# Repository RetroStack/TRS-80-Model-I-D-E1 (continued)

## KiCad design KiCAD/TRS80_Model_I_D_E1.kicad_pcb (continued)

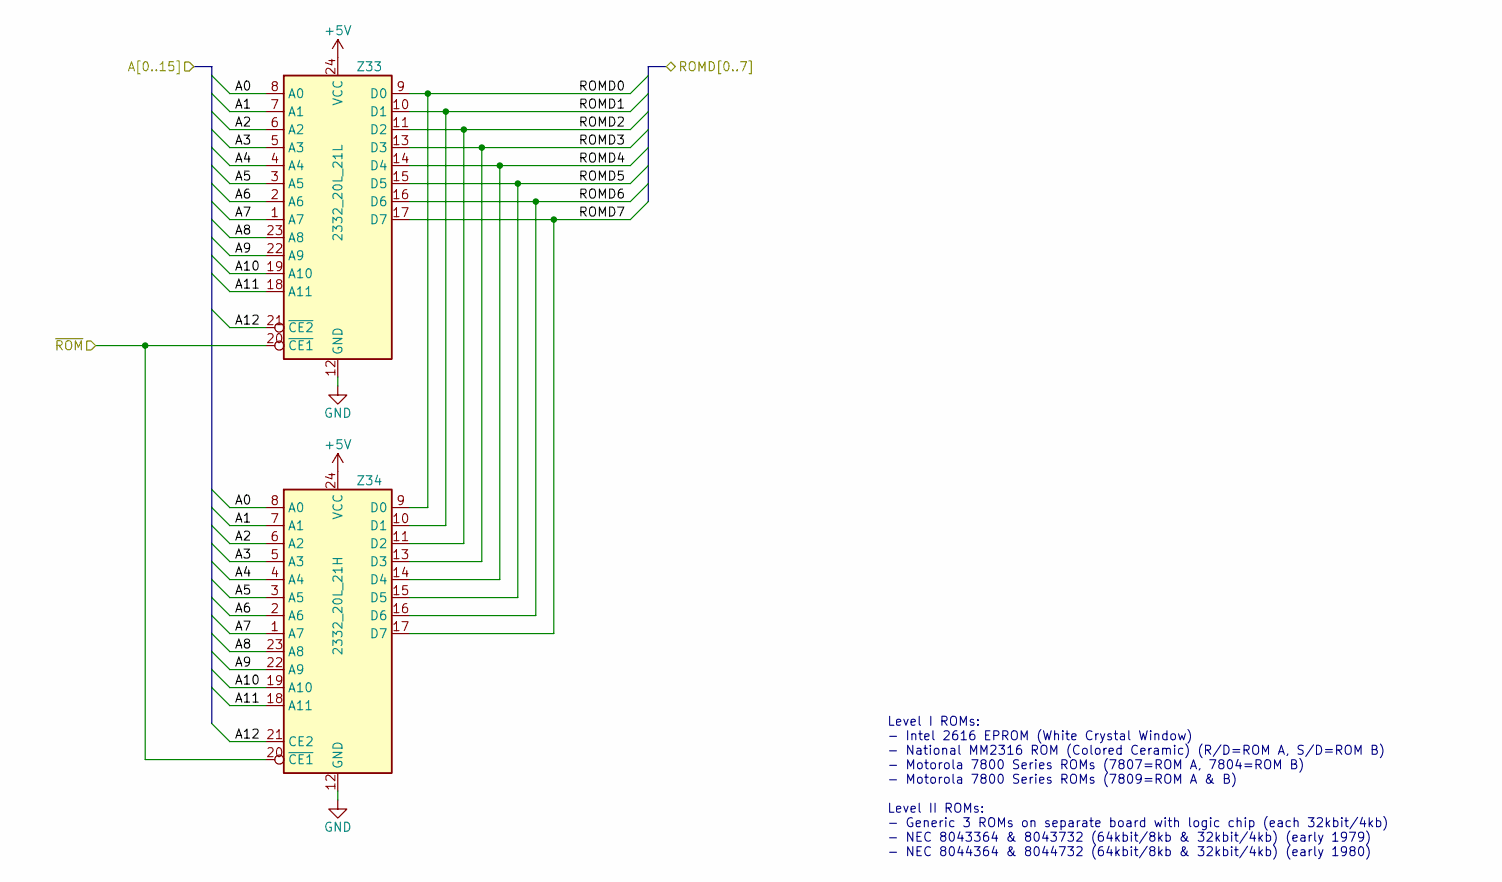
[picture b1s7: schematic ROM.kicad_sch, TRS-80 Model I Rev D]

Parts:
Z33: 2332_20L_21L; TRS80_Model_I_DIP24
Z34: 2332_20L_21H; TRS80_Model_I_DIP24

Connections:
+5V: Z33.24 (VCC), Z34.24 (VCC); also elsewhere on the board
/A0: Z33.8 (A0), Z34.8 (A0); also elsewhere on the board
/A1: Z33.7 (A1), Z34.7 (A1); also elsewhere on the board
/A2: Z33.6 (A2), Z34.6 (A2); also elsewhere on the board
/A3: Z33.5 (A3), Z34.5 (A3); also elsewhere on the board
/A4: Z33.4 (A4), Z34.4 (A4); also elsewhere on the board
/A5: Z33.3 (A5), Z34.3 (A5); also elsewhere on the board
/A6: Z33.2 (A6), Z34.2 (A6); also elsewhere on the board
/A7: Z33.1 (A7), Z34.1 (A7); also elsewhere on the board
/A8: Z33.23 (A8), Z34.23 (A8); also elsewhere on the board
/A9: Z33.22 (A9), Z34.22 (A9); also elsewhere on the board
/A10: Z33.19 (A10), Z34.19 (A10); also elsewhere on the board
/A11: Z33.18 (A11), Z34.18 (A11); also elsewhere on the board
/A12: Z33.21 (A12), Z34.21 (~CE2); also elsewhere on the board
/Address Decoder/~ROM: Z33.20 (~OE), Z34.20 (~CE1); also elsewhere on the board
/RAM-ROM Interface/ROMD0: Z33.9 (D0), Z34.9 (D0); also elsewhere on the board
/RAM-ROM Interface/ROMD1: Z33.10 (D1), Z34.10 (D1); also elsewhere on the board
/RAM-ROM Interface/ROMD2: Z33.11 (D2), Z34.11 (D2); also elsewhere on the board
/RAM-ROM Interface/ROMD3: Z33.13 (D3), Z34.13 (D3); also elsewhere on the board
/RAM-ROM Interface/ROMD4: Z33.14 (D4), Z34.14 (D4); also elsewhere on the board
/RAM-ROM Interface/ROMD5: Z33.15 (D5), Z34.15 (D5); also elsewhere on the board
/RAM-ROM Interface/ROMD6: Z33.16 (D6), Z34.16 (D6); also elsewhere on the board
/RAM-ROM Interface/ROMD7: Z33.17 (D7), Z34.17 (D7); also elsewhere on the board

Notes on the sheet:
Level I ROMs: - Intel 2616 EPROM (White Crystal Window) - National MM2316 ROM (Colored Ceramic) (R/D=ROM A, S/D=ROM B) - Motorola 7800 Series ROMs (7807=ROM A, 7804=ROM B) - Motorola 7800 Series ROMs (7809=ROM A & B) Level II ROMs: - Generic 3 ROMs on separate board with logic chip (each 32kbit/4kb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

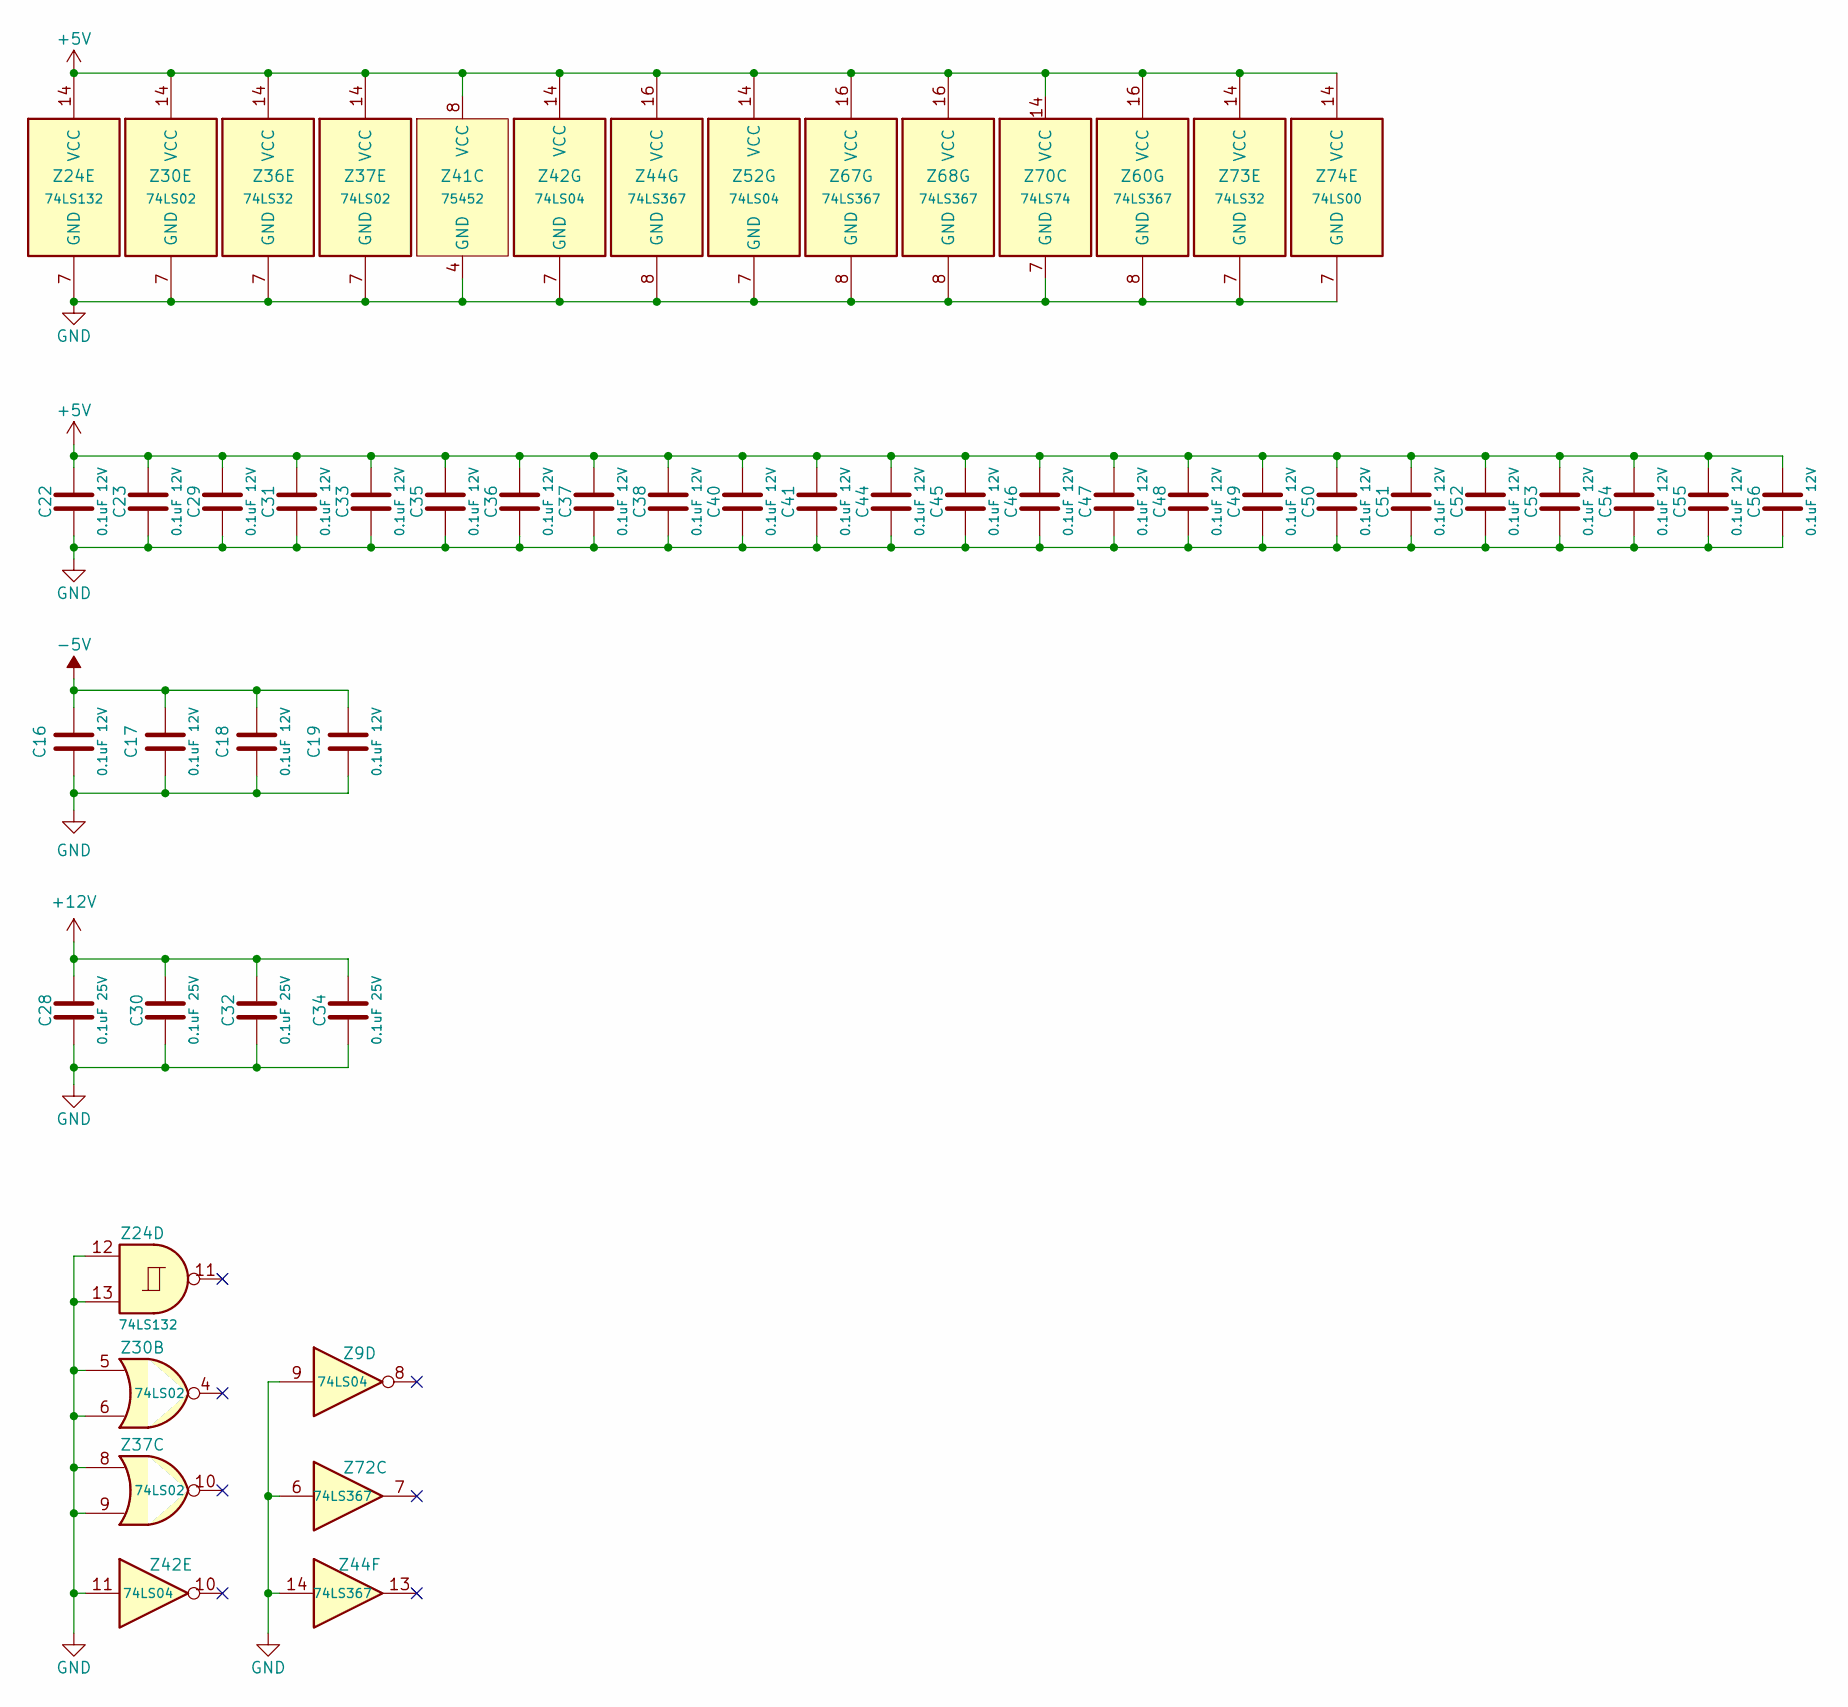
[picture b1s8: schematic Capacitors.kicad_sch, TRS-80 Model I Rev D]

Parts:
C16, C17, C18, C19, C22, C23, C29, C31, C33, C35, C36, C37, C38, C40, C41, C44, C45, C46, C47, C48, C49, C50, C51, C52, C53, C54, C55, C56: 0.1uF 12V; TRS80_Model_I_C_Disc_9.5L_4W_6P_Small
C28, C30, C32, C34: 0.1uF 25V; TRS80_Model_I_C_Disc_18.5L_4W_8.5P_Large
Z9, Z42, Z52: 74LS04; TRS80_Model_I_DIP14
Z24: 74LS132; TRS80_Model_I_DIP14
Z30, Z37: 74LS02; TRS80_Model_I_DIP14
Z36, Z73: 74LS32; TRS80_Model_I_DIP14
Z41: 75452; TRS80_Model_I_DIP8
Z44, Z60, Z67, Z68, Z72: 74LS367; TRS80_Model_I_DIP16
Z70: 74LS74; TRS80_Model_I_DIP14
Z74: 74LS00; TRS80_Model_I_DIP14

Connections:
+5V: C22.1, C23.1, C29.1, C31.1, C33.1, C35.1, C36.1, C37.1, C38.1, C40.1, C41.1, C44.1, C45.1, C46.1, C47.1, C48.1, C49.1, C50.1, C51.1, C52.1, C53.1, C54.1, C55.1, C56.1, Z24.14 (VCC), Z30.14 (VCC), Z36.14 (VCC), Z37.14 (VCC), Z41.8 (VCC), Z42.14 (VCC), Z44.16 (VCC), Z52.14 (VCC), Z60.16 (VCC), Z67.16 (VCC), Z68.16 (VCC), Z70.14 (VCC), Z72.16 (VCC), Z73.14 (VCC), Z74.14 (VCC); also elsewhere on the board
+12V: C28.1, C30.1, C32.1, C34.1; also elsewhere on the board
-5V: C16.1, C17.1, C18.1, C19.1; also elsewhere on the board
unnamed 252: Z24.11; also elsewhere on the board

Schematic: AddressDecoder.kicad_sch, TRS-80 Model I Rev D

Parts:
R48, R61, R62: 4.7k; TRS80_Model_I_R_0.25W
Z3: TRS80_Model_I_DIP16
Z21: 74LS156; TRS80_Model_I_DIP16
Z36, Z73: 74LS32; TRS80_Model_I_DIP14
Z37: 74LS02; TRS80_Model_I_DIP14
Z52: 74LS04; TRS80_Model_I_DIP14
Z74: 74LS00; TRS80_Model_I_DIP14

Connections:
+5V: R48.2, R61.2, R62.2, Z21.16 (VCC); also elsewhere on the board
/A10: Z36.13, Z52.1; also elsewhere on the board
/A11: Z37.5, Z37.6; also elsewhere on the board
/A12: Z21.13 (A0); also elsewhere on the board
/A13: Z21.3 (A1); also elsewhere on the board
/A14: Z21.1 (Ea1), Z21.15 (Eb2); also elsewhere on the board
/A15: Z73.4; also elsewhere on the board
/Address Decoder/~KYBD: Z36.11; also elsewhere on the board
/Address Decoder/~RAM: R62.1, Z3.2, Z3.12, Z3.13, Z3.14, Z3.15, Z21.7 (Q0a), Z74.10; also elsewhere on the board
/Address Decoder/~RAS: Z73.5; also elsewhere on the board
/Address Decoder/~RD: Z52.13; also elsewhere on the board
/Address Decoder/~ROM: R61.1, Z3.6, Z3.7, Z3.8, Z73.9, Z73.12, Z74.9; also elsewhere on the board
/Address Decoder/~VID: Z36.8; also elsewhere on the board
unnamed: Z21.2 (Ea2), Z21.14 (Eb1), Z73.6
unnamed: Z3.10, Z21.9 (Q0b)
unnamed: Z3.3, Z21.6 (Q1a)
unnamed: Z3.9, Z21.10 (Q1b)
unnamed: Z3.4, Z21.5 (Q2a)
unnamed: Z3.11, Z21.11 (Q2b)
unnamed: Z3.5, Z21.4 (Q3a)
unnamed: R48.1, Z21.12 (Q3b), Z36.4
unnamed: Z36.5, Z37.4
unnamed: Z36.9, Z52.2
unnamed: Z36.6, Z36.10, Z36.12
unnamed: Z52.12, Z74.1
unnamed: Z74.2, Z74.8

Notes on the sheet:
38xx..3Bxx
5xxx
4xxx
0001
0000
0111
RAS=0 && A15=0
7xxx
2xxx
0100
0xxx, 1xxx, 2xxx
0011
4xxx..7xxx
0010
0101
3Cxx..3Fxx
0xxx
A14=0
A14=1
0110
6xxx
1xxx
3xxx

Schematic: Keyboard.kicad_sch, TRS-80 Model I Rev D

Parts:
J100: Connection Mainboard Side; TRS80_Model_I_Keyboard_Connector

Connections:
+5V: J100.1; also elsewhere on the board
/A0: J100.5; also elsewhere on the board
/A1: J100.4; also elsewhere on the board
/A2: J100.6; also elsewhere on the board
/A3: J100.9; also elsewhere on the board
/A4: J100.2; also elsewhere on the board
/A5: J100.3; also elsewhere on the board
/A6: J100.7; also elsewhere on the board
/A7: J100.8; also elsewhere on the board
/Address Decoder/~KYBD: J100.14; also elsewhere on the board
/D0: J100.11; also elsewhere on the board
/D1: J100.16; also elsewhere on the board
/D3: J100.13; also elsewhere on the board
/D4: J100.18; also elsewhere on the board
/D5: J100.12; also elsewhere on the board
/D7: J100.17; also elsewhere on the board

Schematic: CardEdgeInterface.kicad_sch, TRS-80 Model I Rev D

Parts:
J4: Edge Connector; TRS80_Model_I_Edge_Connector
R50, R51, R58: 4.7k; TRS80_Model_I_R_0.25W

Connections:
+5V: J4.39, R50.1, R51.1, R58.1; also elsewhere on the board
/A0: J4.25; also elsewhere on the board
/A1: J4.27; also elsewhere on the board
/A2: J4.40; also elsewhere on the board
/A3: J4.34; also elsewhere on the board
/A4: J4.31; also elsewhere on the board
/A5: J4.35; also elsewhere on the board
/A6: J4.38; also elsewhere on the board
/A7: J4.36; also elsewhere on the board
/A8: J4.11; also elsewhere on the board
/A9: J4.17; also elsewhere on the board
/A10: J4.4; also elsewhere on the board
/A11: J4.9; also elsewhere on the board
/A12: J4.5; also elsewhere on the board
/A13: J4.6; also elsewhere on the board
/A14: J4.10; also elsewhere on the board
/A15: J4.7; also elsewhere on the board
/Address Decoder/~RAS: J4.1; also elsewhere on the board
/Address Decoder/~RD: J4.15; also elsewhere on the board
/CPU Gating/MUX: J4.16; also elsewhere on the board
/CPU Gating/~CAS: J4.3; also elsewhere on the board
/CPU Gating/~IN: J4.19; also elsewhere on the board
/CPU Gating/~OUT: J4.12; also elsewhere on the board
/CPU Gating/~TEST: J4.23, R58.2; also elsewhere on the board
/CPU Gating/~WR: J4.13; also elsewhere on the board
/CPU/~INTAK: J4.14; also elsewhere on the board
/CPU/~INT: J4.21, R50.2; also elsewhere on the board
/CPU/~SYSRES: J4.2; also elsewhere on the board
/CPU/~WAIT: J4.33, R51.2; also elsewhere on the board
/D0: J4.30; also elsewhere on the board
/D1: J4.22; also elsewhere on the board
/D3: J4.26; also elsewhere on the board
/D4: J4.18; also elsewhere on the board
/D5: J4.28; also elsewhere on the board
/D7: J4.20; also elsewhere on the board

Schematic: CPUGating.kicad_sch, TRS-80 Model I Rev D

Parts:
Z22, Z38, Z39, Z55, Z72, Z75, Z76: 74LS367; TRS80_Model_I_DIP16
Z52: 74LS04; TRS80_Model_I_DIP14

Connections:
+5V: Z22.16 (VCC), Z38.16 (VCC), Z39.16 (VCC), Z55.16 (VCC), Z75.16 (VCC), Z76.16 (VCC); also elsewhere on the board
/A0: Z55.11; also elsewhere on the board
/A1: Z55.13; also elsewhere on the board
/A2: Z22.11; also elsewhere on the board
/A3: Z22.13; also elsewhere on the board
/A4: Z39.7; also elsewhere on the board
/A5: Z39.9; also elsewhere on the board
/A6: Z39.5; also elsewhere on the board
/A7: Z39.11; also elsewhere on the board
/A8: Z39.3; also elsewhere on the board
/A9: Z39.13; also elsewhere on the board
/A10: Z38.3; also elsewhere on the board
/A11: Z38.13; also elsewhere on the board
/A12: Z38.5; also elsewhere on the board
/A13: Z38.7; also elsewhere on the board
/A14: Z38.11; also elsewhere on the board
/A15: Z38.9; also elsewhere on the board
/Address Decoder/~RAS: Z72.5; also elsewhere on the board
/Address Decoder/~RD: Z22.7; also elsewhere on the board
/CPU Gating/MUX: Z72.3; also elsewhere on the board
/CPU Gating/ZA0: Z55.12; also elsewhere on the board
/CPU Gating/ZA1: Z55.14; also elsewhere on the board
/CPU Gating/ZA2: Z22.12; also elsewhere on the board
/CPU Gating/ZA3: Z22.14; also elsewhere on the board
/CPU Gating/ZA4: Z39.6; also elsewhere on the board
/CPU Gating/ZA5: Z39.10; also elsewhere on the board
/CPU Gating/ZA6: Z39.4; also elsewhere on the board
/CPU Gating/ZA7: Z39.12; also elsewhere on the board
/CPU Gating/ZA8: Z39.2; also elsewhere on the board
/CPU Gating/ZA9: Z39.14; also elsewhere on the board
/CPU Gating/ZA10: Z38.2; also elsewhere on the board
/CPU Gating/ZA11: Z38.14; also elsewhere on the board
/CPU Gating/ZA12: Z38.4; also elsewhere on the board
/CPU Gating/ZA13: Z38.6; also elsewhere on the board
/CPU Gating/ZA14: Z38.12; also elsewhere on the board
/CPU Gating/ZA15: Z38.10; also elsewhere on the board
/CPU Gating/ZD0: Z76.9, Z76.12; also elsewhere on the board
/CPU Gating/ZD1: Z76.3, Z76.14; also elsewhere on the board
/CPU Gating/ZD2: Z75.14, Z76.5; also elsewhere on the board
/CPU Gating/ZD3: Z55.5, Z75.4; also elsewhere on the board
/CPU Gating/ZD4: Z55.3, Z75.6; also elsewhere on the board
/CPU Gating/ZD5: Z55.7, Z75.2; also elsewhere on the board
/CPU Gating/ZD6: Z55.9, Z75.10; also elsewhere on the board
/CPU Gating/ZD7: Z75.12, Z76.7; also elsewhere on the board
/CPU Gating/ZMUX: Z72.2; also elsewhere on the board
/CPU Gating/~CAS: Z72.9; also elsewhere on the board
/CPU Gating/~DBIN: Z55.1, Z76.1; also elsewhere on the board
/CPU Gating/~DBOUT: Z75.1, Z75.15, Z76.15; also elsewhere on the board
/CPU Gating/~IN: Z22.9; also elsewhere on the board
/CPU Gating/~OUT: Z22.3; also elsewhere on the board
/CPU Gating/~TEST: Z52.3; also elsewhere on the board
/CPU Gating/~WR: Z22.5; also elsewhere on the board
/CPU Gating/~ZCAS: Z72.10; also elsewhere on the board
/CPU Gating/~ZIN: Z22.10; also elsewhere on the board
/CPU Gating/~ZOUT: Z22.2; also elsewhere on the board
/CPU Gating/~ZRAS: Z72.4; also elsewhere on the board
/CPU Gating/~ZRD: Z22.6; also elsewhere on the board
/CPU Gating/~ZWR: Z22.4; also elsewhere on the board
/D0: Z76.10, Z76.11; also elsewhere on the board
/D1: Z76.2, Z76.13; also elsewhere on the board
/D3: Z55.4, Z75.5; also elsewhere on the board
/D4: Z55.2, Z75.7; also elsewhere on the board
/D5: Z55.6, Z75.3; also elsewhere on the board
/D7: Z75.11, Z76.6; also elsewhere on the board
unnamed: Z22.1, Z22.15, Z38.1, Z38.15, Z39.1, Z39.15, Z52.4, Z55.15, Z72.1

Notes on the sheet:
Bi-directional Data Bus
Address Bus
Control Signals

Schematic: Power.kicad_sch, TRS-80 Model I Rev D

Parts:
C1: 220uF 16V; TRS80_Model_I_C_Pol_Axial_21L_9W_29P
C3, C14, C15: 0.01uF 24V; TRS80_Model_I_C_Disc_9.5L_4W_6P_Small
C4, C10, C11: 10uF 16V; TRS80_Model_I_C_Pol_Radial_5D_2.5P
C8: 2200uF 35V; TRS80_Model_I_C_Pol_Axial_41L_19W_48P
C9: 10000uF 16V; TRS80_Model_I_C_Pol_Axial_63L_25W_71P
C12, C13: 470pF; TRS80_Model_I_C_Disc_9.5L_4W_6P_Small
CR1: 1N4735; TRS80_Model_I_D
CR2: 1N5231; TRS80_Model_I_D
CR8: MDA202; TRS80_Model_I_D_Bridge
J1: Front View; TRS80_Model_I_DIN5
Q3: TIP29A; TRS80_Model_I_Q_Box_BCE
Q4: 2N6594; TRS80_Model_I_Q_Heatsink_Large_BEC
Q5: 2N3906; TRS80_Model_I_Q_Circle_EBC
Q6: MJE34; TRS80_Model_I_Q_Heatsink_Small_BCE
R1: 68; TRS80_Model_I_R_0.25W
R2: 2.7k; TRS80_Model_I_R_0.25W
R3: 750; TRS80_Model_I_R_0.25W
R4: 0.33; TRS80_Model_I_R_2W
R5, R10: 1k; TRS80_Model_I_R_Pot
R6, R7, R16: 1.2k; TRS80_Model_I_R_0.25W
R8: 100k; TRS80_Model_I_R_0.25W
R9, R11, R12: 3.3k; TRS80_Model_I_R_0.25W
R13: 2.2k; TRS80_Model_I_R_0.25W
R14: 12k; TRS80_Model_I_R_0.25W
R15: 1.5k; TRS80_Model_I_R_0.25W
R17: 2k; TRS80_Model_I_R_0.25W
R18: 5.6; TRS80_Model_I_R_3W
R19: 220; TRS80_Model_I_R_0.5W
S1: TRS80_Model_I_Sw_Large
Z1, Z2: LM723C; TRS80_Model_I_DIP14

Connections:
+5V: C10.1, C14.1, CR1.1 (K), R4.2, R7.1, R8.2, Z1.3 (CSEN); also elsewhere on the board
+12V: C11.1, C15.1, R13.1, R18.1, Z1.11 (VC), Z1.12 (V+), Z2.3 (CSEN); also elsewhere on the board
-5V: C3.1, C4.2, CR2.2 (A), R19.1; also elsewhere on the board
unnamed: C1.2, R19.2, S1.10
unnamed: CR8.1 (+), S1.4, S1.5, S1.8, S1.9
unnamed: CR8.4 (-), S1.11, S1.12
unnamed: CR8.2, J1.1
unnamed: CR8.3, J1.3
unnamed: J1.2, S1.1, S1.2
unnamed: Q3.1 (B), R2.1, Z1.10 (Vout)
unnamed: Q3.2 (C), Q4.1 (B), R1.2
unnamed: Q3.3 (E), Q4.3 (C), R2.2, R3.1, R4.1
unnamed: C9.1, Q4.2 (E), R1.1, S1.6, S1.7
unnamed: Q5.2 (B), R8.1
unnamed: Q5.3 (C), R9.2
unnamed: Q5.1 (E), R5.2, Z1.5 (+)
unnamed: Q6.1 (B), R16.2, Z2.11 (VC)
unnamed: Q6.2 (C), R17.1, R18.2, Z2.10 (Vout)
unnamed: C8.1, Q6.3 (E), R16.1, S1.3, Z2.12 (V+)
unnamed: R5.1, R6.1
unnamed: R10.1, R12.1
unnamed: R10.3, R13.2
unnamed: R5.3, R11.1
unnamed: C12.1, R7.2, Z1.4 (-)
unnamed: C12.2, Z1.13 (FC)
unnamed: R3.2, R9.1, Z1.2 (ILIM)
unnamed: R6.2, Z1.6 (VREF)
unnamed: R15.2, Z2.5 (+)
unnamed: C13.2, R10.2, Z2.4 (-)
unnamed: C13.1, Z2.13 (FC)
unnamed: R14.1, R17.2, Z2.2 (ILIM)
unnamed: R15.1, Z2.6 (VREF)

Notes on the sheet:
12V-20V AC 1A
0.5W
14V-20V DC 350mA

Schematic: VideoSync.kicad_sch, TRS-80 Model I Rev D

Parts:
C20: 330pF; TRS80_Model_I_C_Disc_9.5L_4W_6P_Small
C21: 750pF; TRS80_Model_I_C_Disc_9.5L_4W_6P_Small
C26: 0.047uF; TRS80_Model_I_C_Box_11L_5W_6P_Large
C27: 0.022uF; TRS80_Model_I_C_Box_7.5L_5W_4.5P_Small
R20, R21: 100k; TRS80_Model_I_R_Pot
R43, R44: 10k; TRS80_Model_I_R_0.25W
Z5: 74C00; TRS80_Model_I_DIP14
Z6, Z57: 74C04; TRS80_Model_I_DIP14

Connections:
+5V: Z5.14 (VCC), Z6.14 (VCC), Z57.14 (VCC); also elsewhere on the board
/Video/Video Counter/HDRV: Z6.13; also elsewhere on the board
/Video/Video Counter/VDRV: Z57.1; also elsewhere on the board
/Video/Video Mixer/SYNC: Z5.8; also elsewhere on the board
unnamed: C20.1, R20.2, Z6.3
unnamed: C20.2, C21.1, Z6.6
unnamed: C21.2, R43.1, Z6.11
unnamed: C26.1, R21.2, Z57.13
unnamed: C26.2, C27.1, Z57.10
unnamed: C27.2, R44.2, Z57.5
unnamed: R20.1, Z6.2
unnamed: R21.1, Z57.4
unnamed: Z5.1, Z5.5, Z57.8
unnamed: Z5.6, Z5.9
unnamed: Z5.10, Z5.11
unnamed: Z5.3, Z5.4, Z5.12
unnamed: Z5.2, Z5.13, Z6.8
unnamed: Z6.1, Z6.12
unnamed: Z6.4, Z6.5
unnamed: Z6.9, Z6.10
unnamed: Z57.2, Z57.3
unnamed: Z57.6, Z57.9
unnamed: Z57.11, Z57.12

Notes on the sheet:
Amplifier
Sync Offset
H-Sync
V-Sync Offset Capacitor
V-Sync
Inv-Sync
H-Sync Offset Capacitor
Sync Pulse Length
V-Sync Length
V-Sync Offset Resistor
H-Sync Length
Combine Sync Signals
H-Sync Offset Resistor

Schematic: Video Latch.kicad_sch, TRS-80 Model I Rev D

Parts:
R39: 4.7k; TRS80_Model_I_R_0.25W
Z7: 74LS74; TRS80_Model_I_DIP14
Z27: 74LS175; TRS80_Model_I_DIP16
Z28: 74LS174; TRS80_Model_I_DIP16
Z30: 74LS02; TRS80_Model_I_DIP14
Z42: 74LS04; TRS80_Model_I_DIP14

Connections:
+5V: R39.2, Z7.14 (VCC), Z27.16 (VCC), Z28.16 (VCC); also elsewhere on the board
/Address Decoder/~VID: Z7.4 (~S); also elsewhere on the board
/Video/Video Counter/HDRV: Z30.8; also elsewhere on the board
/Video/Video Counter/L3: Z27.12 (D2); also elsewhere on the board
/Video/Video Counter/VDRV: Z30.9; also elsewhere on the board
/Video/Video Counter/~LATCH: Z7.3 (C), Z27.9 (Cp), Z28.9 (Cp); also elsewhere on the board
/Video/Video Generator/GRAPHICS: Z27.3 (~Q0); also elsewhere on the board
/Video/Video Generator/LB0: Z28.15 (Q5); also elsewhere on the board
/Video/Video Generator/LB1: Z28.12 (Q4); also elsewhere on the board
/Video/Video Generator/LB2: Z28.2 (Q0); also elsewhere on the board
/Video/Video Generator/LB3: Z28.7 (Q2); also elsewhere on the board
/Video/Video Generator/LB4: Z28.5 (Q1); also elsewhere on the board
/Video/Video Generator/LB5: Z28.10 (Q3); also elsewhere on the board
/Video/Video Generator/LB6: Z27.15 (Q3); also elsewhere on the board
/Video/Video Generator/~BLANK: Z27.7 (Q1); also elsewhere on the board
/Video/Video Generator/~CHARGAP: Z27.11 (~Q2); also elsewhere on the board
/Video/Video Generator/~GRAPHICS: Z27.2 (Q0); also elsewhere on the board
/Video/Video Latch/VD0: Z28.14 (D5); also elsewhere on the board
/Video/Video Latch/VD1: Z28.13 (D4); also elsewhere on the board
/Video/Video Latch/VD2: Z28.3 (D0); also elsewhere on the board
/Video/Video Latch/VD3: Z28.6 (D2); also elsewhere on the board
/Video/Video Latch/VD4: Z28.4 (D1); also elsewhere on the board
/Video/Video Latch/VD5: Z28.11 (D3); also elsewhere on the board
/Video/Video Latch/VD6: Z27.13 (D3); also elsewhere on the board
/Video/Video Latch/VD7: Z42.13; also elsewhere on the board
/Video/Video Latch/~VCLR: Z7.6 (~Q), Z27.1 (~Mr), Z28.1 (~Mr)
unnamed: R39.1, Z7.1 (~R)
unnamed: Z27.4 (D0), Z42.12
unnamed: Z27.5 (D1), Z30.10

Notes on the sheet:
CHARGAP
GRAPHICS
Clear when CPU drives
~{BLANK}
~{GRAPHICS}

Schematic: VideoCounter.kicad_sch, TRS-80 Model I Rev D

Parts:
Z12, Z32, Z50, Z65: 74LS93; TRS80_Model_I_DIP14
Z24: 74LS132; TRS80_Model_I_DIP14
Z43: 74LS157; TRS80_Model_I_DIP16
Z58: 74LS92; TRS80_Model_I_DIP14
Z66: 74LS11; TRS80_Model_I_DIP14
Z70: 74LS74; TRS80_Model_I_DIP14

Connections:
+5V: Z12.5 (VCC), Z32.5 (VCC), Z43.16 (VCC), Z50.5 (VCC), Z58.5 (VCC), Z65.5 (VCC), Z66.14 (VCC); also elsewhere on the board
/CPU/CLK: Z43.3 (I1a), Z70.11 (C); also elsewhere on the board
/CPU/HI: Z70.10 (~S), Z70.13 (~R); also elsewhere on the board
/Video/Video Access Multiplexer/C0: Z43.7 (Zb); also elsewhere on the board
/Video/Video Access Multiplexer/C1: Z65.9 (Q1); also elsewhere on the board
/Video/Video Access Multiplexer/C2: Z50.14 (CP0), Z65.8 (Q2); also elsewhere on the board
/Video/Video Access Multiplexer/C3: Z50.1 (CP1..3), Z50.12 (Q0); also elsewhere on the board
/Video/Video Access Multiplexer/C4: Z50.9 (Q1), Z66.3; also elsewhere on the board
/Video/Video Access Multiplexer/C5: Z50.8 (Q2), Z66.5; also elsewhere on the board
/Video/Video Access Multiplexer/R0: Z32.14 (CP0), Z65.12 (Q0); also elsewhere on the board
/Video/Video Access Multiplexer/R1: Z32.1 (CP1..3), Z32.12 (Q0), Z66.13; also elsewhere on the board
/Video/Video Access Multiplexer/R2: Z32.9 (Q1), Z66.2; also elsewhere on the board
/Video/Video Access Multiplexer/R3: Z32.8 (Q2); also elsewhere on the board
/Video/Video Counter/HDRV: Z12.14 (CP0), Z50.11 (Q3), Z66.4; also elsewhere on the board
/Video/Video Counter/L0: Z12.1 (CP1..3), Z12.12 (Q0); also elsewhere on the board
/Video/Video Counter/L1: Z12.9 (Q1); also elsewhere on the board
/Video/Video Counter/L2: Z12.8 (Q2), Z66.9, Z66.10; also elsewhere on the board
/Video/Video Counter/L3: Z12.11 (Q3), Z65.14 (CP0), Z66.11; also elsewhere on the board
/Video/Video Counter/VDRV: Z32.11 (Q3), Z66.1; also elsewhere on the board
/Video/Video Counter/~LATCH: Z24.3; also elsewhere on the board
unnamed: Z12.2 (R0(1)), Z12.3 (R0(2)), Z66.8
unnamed: Z32.2 (R0(1)), Z32.3 (R0(2)), Z66.12
unnamed: Z43.2 (I0a), Z70.9 (Q)
unnamed: Z24.2, Z43.11 (I0c), Z58.9 (Q2)
unnamed: Z43.6 (I1b), Z43.10 (I1c), Z58.8 (Q3)
unnamed: Z43.9 (Zc), Z65.1 (CP1..3)
unnamed: Z50.2 (R0(1)), Z50.3 (R0(2)), Z66.6
unnamed: Z24.1, Z58.1 (CP1..3), Z58.12 (Q0)
unnamed: Z70.8 (~Q), Z70.12 (D)

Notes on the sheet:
BIT 1
7.92 kHz
CLK/2
660 Hz
CP0/2
1.98 kHz
60 Hz
887.042 kHz
1.32 kHz
Character line counter
82.5 Hz
27.72 kHz
Mode Selector
CP0/11
3.96 kHz
110.88 kHz
CP1/4
221.76 kHz
55.44 kHz
15.84 kHz
CP0/6
CP0/12
BIT 3
330 Hz
Column counter
Row counter
10.6445 MHz
5.322 MHz
443.52 kHz
CP0/14
165 Hz
Every 6th count

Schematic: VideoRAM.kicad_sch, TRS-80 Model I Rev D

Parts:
Z30: 74LS02; TRS80_Model_I_DIP14
Z44, Z60: 74LS367; TRS80_Model_I_DIP16
Z45, Z46, Z47, Z48, Z61, Z62, Z63: 2102; TRS80_Model_I_DIP16

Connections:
+5V: Z45.10 (VCC), Z46.10 (VCC), Z47.10 (VCC), Z48.10 (VCC), Z60.16 (VCC), Z61.10 (VCC), Z62.10 (VCC), Z63.10 (VCC); also elsewhere on the board
/D0: Z44.7, Z48.11 (IN); also elsewhere on the board
/D1: Z44.5, Z47.11 (IN); also elsewhere on the board
/D3: Z44.9, Z45.11 (IN); also elsewhere on the board
/D4: Z60.9, Z61.11 (IN); also elsewhere on the board
/D5: Z60.7, Z62.11 (IN); also elsewhere on the board
/D7: Z60.3, Z63.11 (IN); also elsewhere on the board
/Video/Video Access Multiplexer/VA0: Z45.8 (A0), Z46.8 (A0), Z47.8 (A0), Z48.8 (A0), Z61.8 (A0), Z62.8 (A0), Z63.8 (A0); also elsewhere on the board
/Video/Video Access Multiplexer/VA1: Z45.4 (A1), Z46.4 (A1), Z47.4 (A1), Z48.4 (A1), Z61.4 (A1), Z62.4 (A1), Z63.4 (A1); also elsewhere on the board
/Video/Video Access Multiplexer/VA2: Z45.5 (A2), Z46.5 (A2), Z47.5 (A2), Z48.5 (A2), Z61.5 (A2), Z62.5 (A2), Z63.5 (A2); also elsewhere on the board
/Video/Video Access Multiplexer/VA3: Z45.6 (A3), Z46.6 (A3), Z47.6 (A3), Z48.6 (A3), Z61.6 (A3), Z62.6 (A3), Z63.6 (A3); also elsewhere on the board
/Video/Video Access Multiplexer/VA4: Z45.7 (A4), Z46.7 (A4), Z47.7 (A4), Z48.7 (A4), Z61.7 (A4), Z62.7 (A4), Z63.7 (A4); also elsewhere on the board
/Video/Video Access Multiplexer/VA5: Z45.2 (A5), Z46.2 (A5), Z47.2 (A5), Z48.2 (A5), Z61.2 (A5), Z62.2 (A5), Z63.2 (A5); also elsewhere on the board
/Video/Video Access Multiplexer/VA6: Z45.1 (A6), Z46.1 (A6), Z47.1 (A6), Z48.1 (A6), Z61.1 (A6), Z62.1 (A6), Z63.1 (A6); also elsewhere on the board
/Video/Video Access Multiplexer/VA7: Z45.16 (A7), Z46.16 (A7), Z47.16 (A7), Z48.16 (A7), Z61.16 (A7), Z62.16 (A7), Z63.16 (A7); also elsewhere on the board
/Video/Video Access Multiplexer/VA8: Z45.15 (A8), Z46.15 (A8), Z47.15 (A8), Z48.15 (A8), Z61.15 (A8), Z62.15 (A8), Z63.15 (A8); also elsewhere on the board
/Video/Video Access Multiplexer/VA9: Z45.14 (A9), Z46.14 (A9), Z47.14 (A9), Z48.14 (A9), Z61.14 (A9), Z62.14 (A9), Z63.14 (A9); also elsewhere on the board
/Video/Video Access Multiplexer/~VRD: Z44.1, Z60.1; also elsewhere on the board
/Video/Video Access Multiplexer/~VWR: Z45.3 (R/~W), Z46.3 (R/~W), Z47.3 (R/~W), Z48.3 (R/~W), Z61.3 (R/~W), Z62.3 (R/~W), Z63.3 (R/~W); also elsewhere on the board
/Video/Video Latch/VD0: Z44.6, Z48.12 (OUT); also elsewhere on the board
/Video/Video Latch/VD1: Z44.4, Z47.12 (OUT); also elsewhere on the board
/Video/Video Latch/VD2: Z44.2, Z46.12 (OUT); also elsewhere on the board
/Video/Video Latch/VD3: Z44.10, Z45.12 (OUT); also elsewhere on the board
/Video/Video Latch/VD4: Z60.10, Z61.12 (OUT); also elsewhere on the board
/Video/Video Latch/VD5: Z30.12, Z60.6, Z62.12 (OUT); also elsewhere on the board
/Video/Video Latch/VD6: Z30.13, Z60.4; also elsewhere on the board
/Video/Video Latch/VD7: Z30.11, Z60.2, Z63.12 (OUT); also elsewhere on the board

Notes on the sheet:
Derived BIT 6
BIT 5
BIT 7

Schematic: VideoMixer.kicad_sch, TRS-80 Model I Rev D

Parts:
C2: 10uF 16V; TRS80_Model_I_C_Pol_Radial_5D_2.5P
C7: 0.01uF 24V; TRS80_Model_I_C_Disc_9.5L_4W_6P_Small
J2: Front View; TRS80_Model_I_DIN5
Q1: 2N3904; TRS80_Model_I_Q_Circle_EBC
Q2: 2N3906; TRS80_Model_I_Q_Circle_EBC
R22: 75; TRS80_Model_I_R_0.25W
R23: 120; TRS80_Model_I_R_0.25W
R27: 330; TRS80_Model_I_R_0.25W
R28: 270; TRS80_Model_I_R_0.25W
R29: 1.8k; TRS80_Model_I_R_0.25W
R30: 47; TRS80_Model_I_R_0.25W
Z41: 75452; TRS80_Model_I_DIP8

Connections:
+5V: J2.1, Q2.1 (E), R30.1; also elsewhere on the board
/Video/Video Generator/PIXEL: Z41.6 (2A), Z41.7 (2B); also elsewhere on the board
/Video/Video Mixer/SYNC: R29.1; also elsewhere on the board
unnamed: Q1.2 (B), R23.1, R27.1, R28.2
unnamed: C2.1, C7.1, Q1.3 (C), R30.2
unnamed: J2.4, Q1.1 (E), R22.1
unnamed: Q2.2 (B), R29.2
unnamed: Q2.3 (C), R28.1
unnamed: R23.2, Z41.5 (2Y)

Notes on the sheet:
Q2 open, Z41 any => 0V (sync level) Q2 closed, Z41 closed => 1.23V (black level) - R28 with series resistors R23 & R27 Q2 closed, Z41 open => 2.75V (white level) - Only R27 & R28

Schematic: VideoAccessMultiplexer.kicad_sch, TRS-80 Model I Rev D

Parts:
R49: 4.7k; TRS80_Model_I_R_0.25W
Z31, Z49, Z64: 74LS157; TRS80_Model_I_DIP16

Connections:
+5V: R49.1, Z31.16 (VCC), Z49.16 (VCC), Z64.16 (VCC); also elsewhere on the board
/A0: Z64.11 (I0c); also elsewhere on the board
/A1: Z64.2 (I0a); also elsewhere on the board
/A2: Z64.14 (I0d); also elsewhere on the board
/A3: Z64.5 (I0b); also elsewhere on the board
/A4: Z49.11 (I0c); also elsewhere on the board
/A5: Z49.2 (I0a); also elsewhere on the board
/A6: Z31.11 (I0c); also elsewhere on the board
/A7: Z31.14 (I0d); also elsewhere on the board
/A8: Z31.2 (I0a); also elsewhere on the board
/A9: Z31.5 (I0b); also elsewhere on the board
/Address Decoder/~RD: Z49.5 (I0b); also elsewhere on the board
/Address Decoder/~VID: Z31.1 (S), Z49.1 (S), Z64.1 (S); also elsewhere on the board
/CPU Gating/~WR: Z49.14 (I0d); also elsewhere on the board
/Video/Video Access Multiplexer/C0: Z64.10 (I1c); also elsewhere on the board
/Video/Video Access Multiplexer/C1: Z64.3 (I1a); also elsewhere on the board
/Video/Video Access Multiplexer/C2: Z64.13 (I1d); also elsewhere on the board
/Video/Video Access Multiplexer/C3: Z64.6 (I1b); also elsewhere on the board
/Video/Video Access Multiplexer/C4: Z49.10 (I1c); also elsewhere on the board
/Video/Video Access Multiplexer/C5: Z49.3 (I1a); also elsewhere on the board
/Video/Video Access Multiplexer/R0: Z31.10 (I1c); also elsewhere on the board
/Video/Video Access Multiplexer/R1: Z31.13 (I1d); also elsewhere on the board
/Video/Video Access Multiplexer/R2: Z31.3 (I1a); also elsewhere on the board
/Video/Video Access Multiplexer/R3: Z31.6 (I1b); also elsewhere on the board
/Video/Video Access Multiplexer/VA0: Z64.9 (Zc); also elsewhere on the board
/Video/Video Access Multiplexer/VA1: Z64.4 (Za); also elsewhere on the board
/Video/Video Access Multiplexer/VA2: Z64.12 (Zd); also elsewhere on the board
/Video/Video Access Multiplexer/VA3: Z64.7 (Zb); also elsewhere on the board
/Video/Video Access Multiplexer/VA4: Z49.9 (Zc); also elsewhere on the board
/Video/Video Access Multiplexer/VA5: Z49.4 (Za); also elsewhere on the board
/Video/Video Access Multiplexer/VA6: Z31.9 (Zc); also elsewhere on the board
/Video/Video Access Multiplexer/VA7: Z31.12 (Zd); also elsewhere on the board
/Video/Video Access Multiplexer/VA8: Z31.4 (Za); also elsewhere on the board
/Video/Video Access Multiplexer/VA9: Z31.7 (Zb); also elsewhere on the board
/Video/Video Access Multiplexer/~VRD: Z49.7 (Zb); also elsewhere on the board
/Video/Video Access Multiplexer/~VWR: Z49.12 (Zd); also elsewhere on the board
unnamed: R49.2, Z49.6 (I1b), Z49.13 (I1d)

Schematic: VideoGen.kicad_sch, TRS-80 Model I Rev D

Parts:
R40: 4.7k; TRS80_Model_I_R_0.25W
Z8: 74LS153; TRS80_Model_I_DIP16
Z9, Z42: 74LS04; TRS80_Model_I_DIP14
Z10, Z11: 74LS166; TRS80_Model_I_DIP16
Z26: 74LS20; TRS80_Model_I_DIP14
Z29: MCM6670; TRS80_Model_I_DIP18
Z30: 74LS02; TRS80_Model_I_DIP14

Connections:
+5V: R40.2, Z8.16 (VCC), Z9.14 (VCC), Z10.16 (VCC), Z11.16 (VCC), Z26.14 (VCC), Z29.18 (VCC); also elsewhere on the board
/Video/Video Counter/L0: Z29.11 (R0); also elsewhere on the board
/Video/Video Counter/L1: Z29.10 (R1); also elsewhere on the board
/Video/Video Counter/L2: Z8.14 (S0), Z29.8 (R2); also elsewhere on the board
/Video/Video Counter/L3: Z8.2 (S1); also elsewhere on the board
/Video/Video Counter/~LATCH: Z9.3; also elsewhere on the board
/Video/Video Generator/GRAPHICS: Z26.4; also elsewhere on the board
/Video/Video Generator/LB0: Z8.6 (I0a), Z29.7 (A0); also elsewhere on the board
/Video/Video Generator/LB1: Z8.10 (I0b), Z29.6 (A1); also elsewhere on the board
/Video/Video Generator/LB2: Z8.5 (I1a), Z29.5 (A2); also elsewhere on the board
/Video/Video Generator/LB3: Z8.11 (I1b), Z29.4 (A3); also elsewhere on the board
/Video/Video Generator/LB4: Z8.4 (I2a), Z29.3 (A4); also elsewhere on the board
/Video/Video Generator/LB5: Z8.12 (I2b), Z29.2 (A5); also elsewhere on the board
/Video/Video Generator/LB6: Z29.1 (A6); also elsewhere on the board
/Video/Video Generator/PIXEL: Z30.1; also elsewhere on the board
/Video/Video Generator/~BLANK: Z26.1, Z26.2, Z26.9; also elsewhere on the board
/Video/Video Generator/~CHARGAP: Z26.12; also elsewhere on the board
/Video/Video Generator/~GRAPHICS: Z26.10; also elsewhere on the board
unnamed: Z10.4 (C), Z29.12 (D0)
unnamed: R40.1, Z10.9 (Clr), Z11.9 (Clr)
unnamed: Z10.5 (D), Z29.13 (D1)
unnamed: Z10.10 (E), Z29.14 (D2)
unnamed: Z10.11 (F), Z29.15 (D3)
unnamed: Z10.12 (G), Z29.16 (D4)
unnamed: Z10.15 (PE), Z26.8
unnamed: Z10.13 (Qh), Z30.3
unnamed: Z8.9 (Zb), Z11.4 (C), Z11.5 (D), Z11.10 (E)
unnamed: Z8.7 (Za), Z11.11 (F), Z11.12 (G), Z11.14 (H)
unnamed: Z11.15 (PE), Z26.6
unnamed: Z11.13 (Qh), Z30.2
unnamed: Z9.4, Z26.5, Z26.13

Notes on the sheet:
ASCII
SHIFT/~{LOAD}
LATCH
Right
GRAPHICS PIXEL
Left
Character Generator
GRAPHICS
~{SHIFT}
ASCII PIXEL
Inversed Clock (delays clock)

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
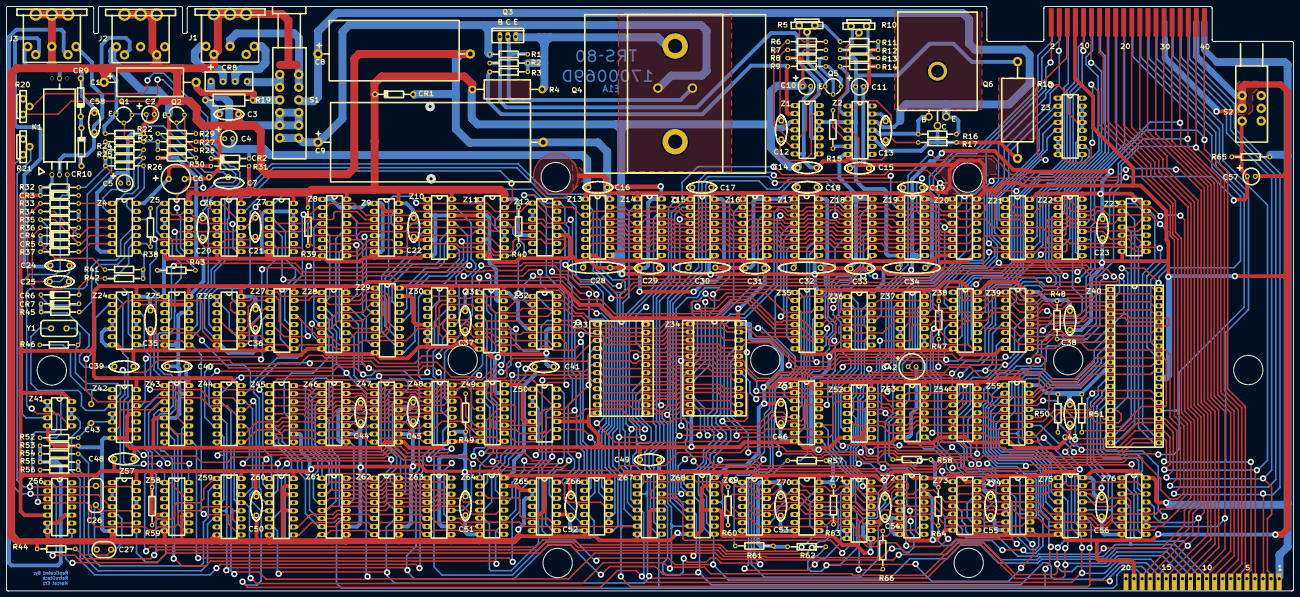
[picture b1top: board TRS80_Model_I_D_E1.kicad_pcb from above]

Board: 2 copper layers, 405.6 x 184.2 mm, 225 parts (0 on the bottom side), 304 nets.
